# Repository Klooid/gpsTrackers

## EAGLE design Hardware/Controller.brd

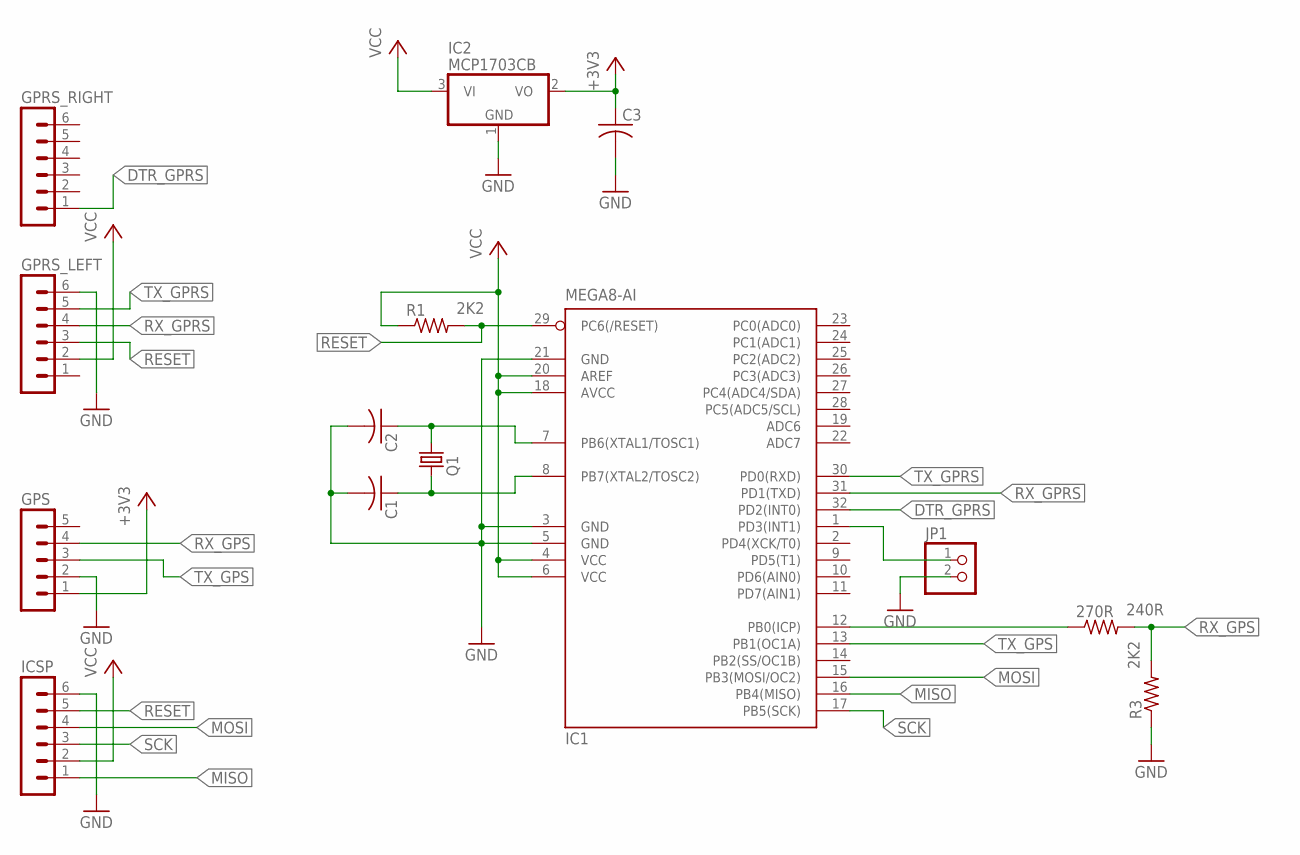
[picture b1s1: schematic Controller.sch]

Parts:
270R: 240R; M0805
C1, C2, C3: C-US025-024X044; C025-024X044
GPRS_LEFT: MA06-1
GPRS_RIGHT: MA06-1
GPS: MA05-1
IC1: MEGA8-AI; TQFP32-08
IC2: MCP1703CB; SOT23
ICSP: MA06-1
JP1: PINHD-1X2; 1X02
Q1: CRYSTALHC49U-V; HC49U-V
R1, R3: 2K2; M0805

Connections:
+3V3: C3.1, GPS.1, IC2.2 (VO)
DTR_GPRS: GPRS_RIGHT.1, IC1.32 (PD2(INT0))
GND: C1.2, C2.2, C3.2, GPRS_LEFT.6, GPS.2, IC1.3 (GND), IC1.5 (GND), IC1.21 (GND), IC2.1 (GND), ICSP.6, JP1.2, R3.1
MISO: IC1.16 (PB4(MISO)), ICSP.1
MOSI: IC1.15 (PB3(MOSI/OC2)), ICSP.4
unnamed: C2.1, IC1.7 (PB6(XTAL1/TOSC1)), Q1.2
unnamed: C1.1, IC1.8 (PB7(XTAL2/TOSC2)), Q1.1
unnamed: IC1.1 (PD3(INT1)), JP1.1
NODEGPSTX: 270R.1, IC1.12 (PB0(ICP))
RESET: GPRS_LEFT.3, IC1.29 (PC6(/RESET)), ICSP.5, R1.2
RX_GPRS: GPRS_LEFT.4, IC1.31 (PD1(TXD))
RX_GPS: 270R.2, GPS.4, R3.2
SCK: IC1.17 (PB5(SCK)), ICSP.3
TX_GPRS: GPRS_LEFT.5, IC1.30 (PD0(RXD))
TX_GPS: GPS.3, IC1.13 (PB1(OC1A))
VCC: GPRS_LEFT.2, IC1.4 (VCC), IC1.6 (VCC), IC1.18 (AVCC), IC1.20 (AREF), IC2.3 (VI), ICSP.2, R1.1

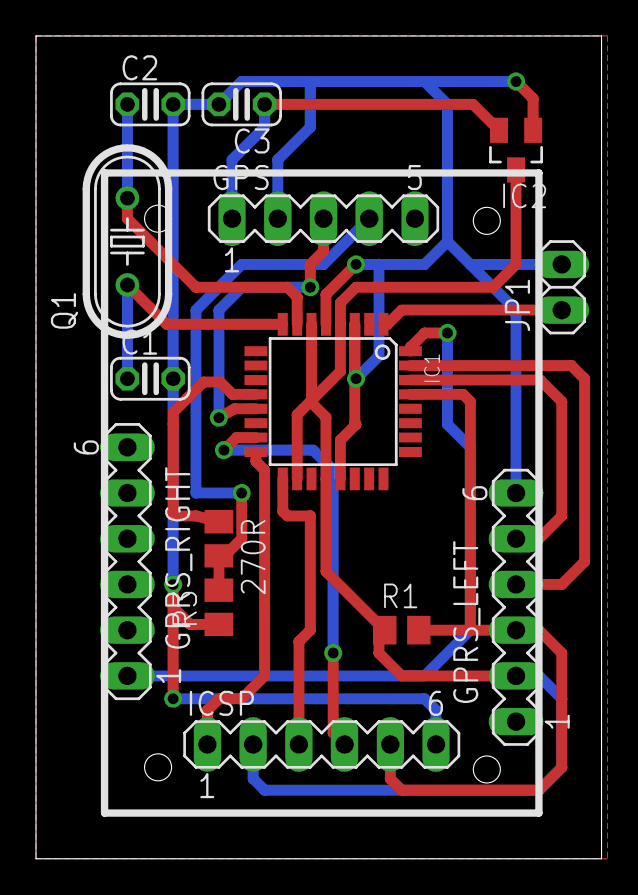
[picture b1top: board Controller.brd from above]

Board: 2 copper layers, 31.4 x 45.7 mm, 14 parts (0 on the bottom side), 16 nets.

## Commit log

2017-01-28 :lollipop: Added .gitattributes & .gitignore files
2017-03-12 Posteo de valores
2017-03-12 Agregar comandos GPRS para verificar y recibir informacion
2017-03-13 Trabajo en pruebas y placa
2017-03-14 Añadir Booteo
